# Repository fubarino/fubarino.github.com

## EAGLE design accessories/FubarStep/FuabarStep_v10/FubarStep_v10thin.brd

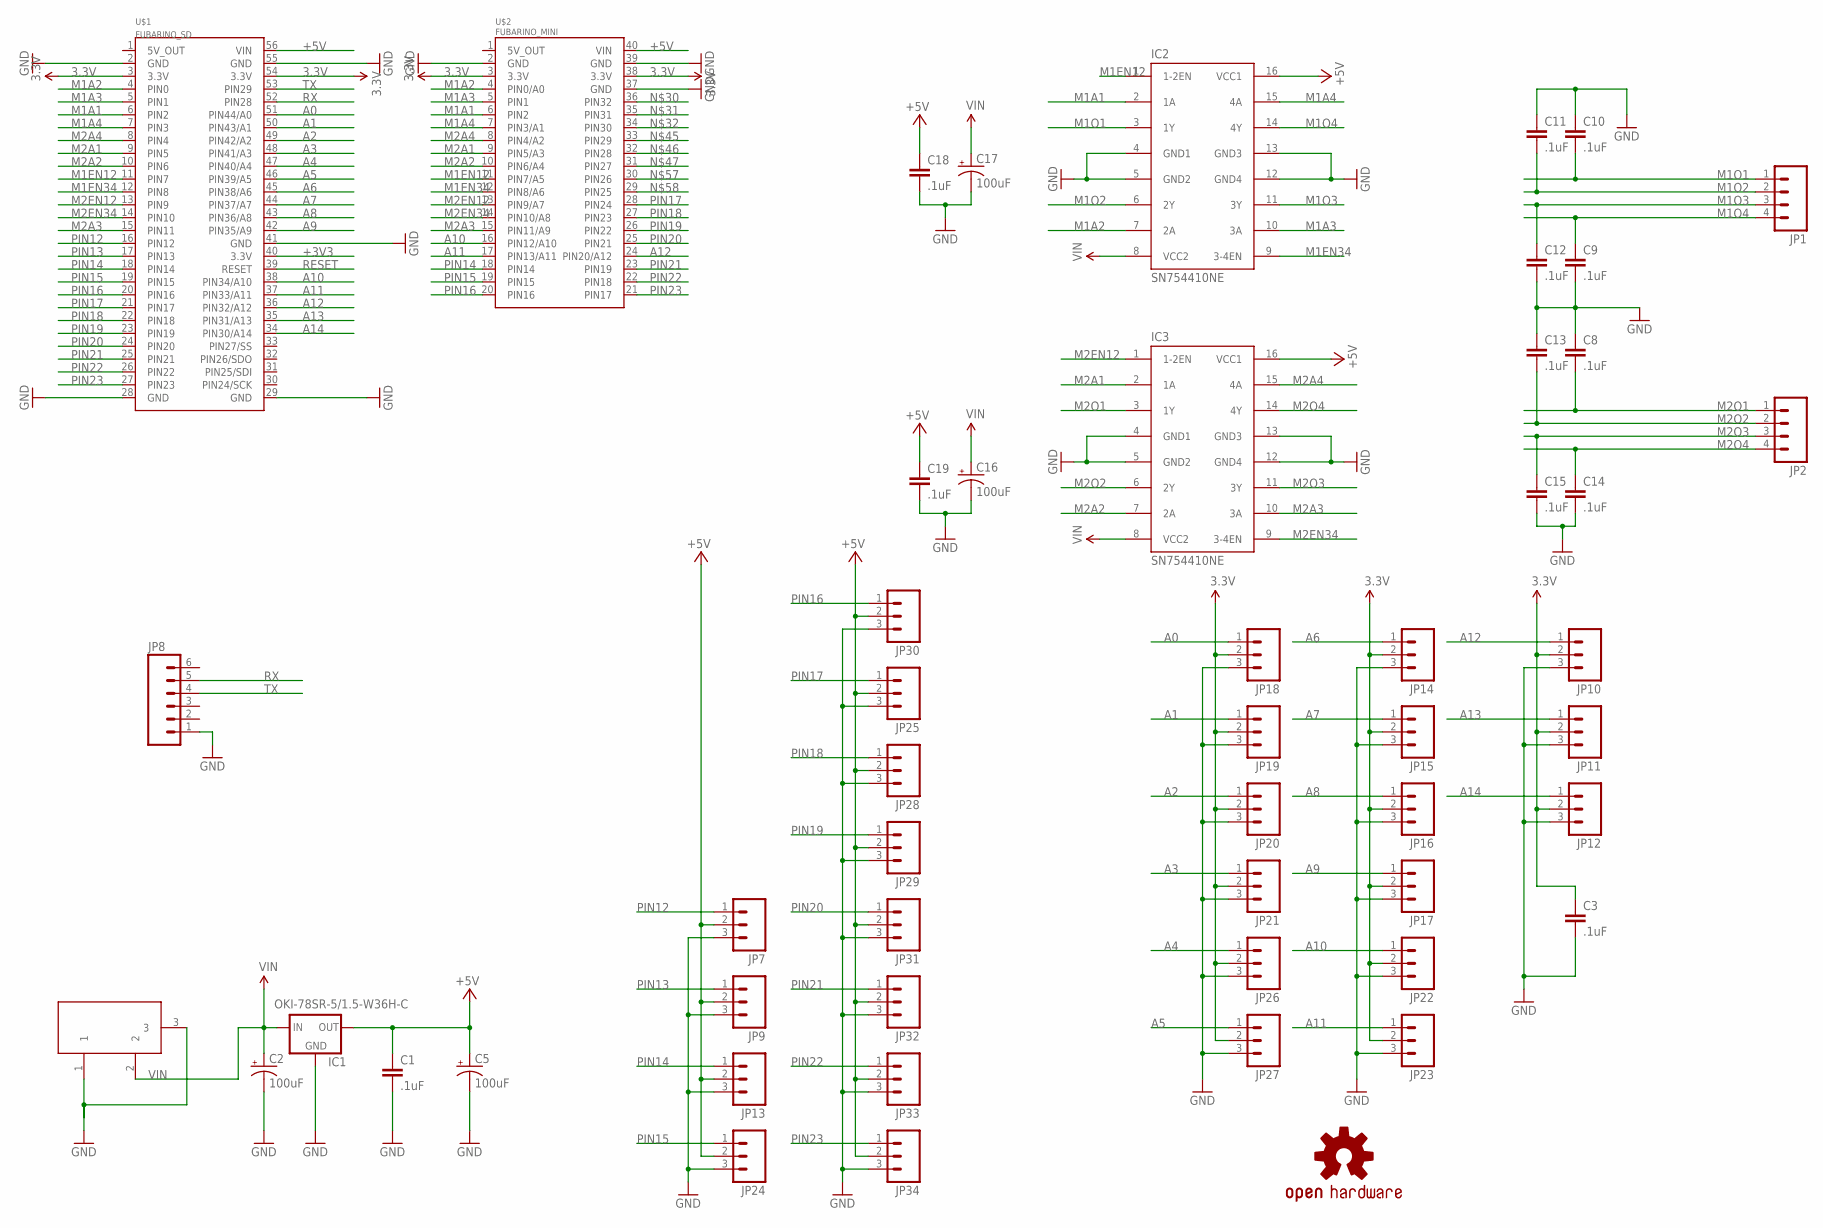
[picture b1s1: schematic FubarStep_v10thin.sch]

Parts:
C1, C3, C8, C9, C10, C11, C12, C13, C14, C15, C18, C19: .1uF; CAP-PTH-SMALL
C2, C5, C16, C17: 100uF; CPOL-RADIAL-100UF-25V
IC1: OKI-78SR-5/1.5-W36H-C; TO220-IGO
IC2, IC3: SN754410NE; DIL16
JP1, JP2: M04SCREW_LOCK; SCREWTERMINAL-3.5MM-4_LOCK
JP7, JP9, JP10, JP11, JP12, JP13, JP14, JP15, JP16, JP17, JP18, JP19, JP20, JP21, JP22, JP23, JP24, JP25, JP26, JP27, JP28, JP29, JP30, JP31, JP32, JP33, JP34: M03PTH; 1X03
JP8: M06LOCK; 1X06_LOCK
LOGO1: OSHW-LOGOM; OSHW-LOGO-M
U$1: FUBARINO_SD
U$2: FUBARINO_MINI
X1: DC21MMX; DC-21MM

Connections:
3.3V: C3.1, JP10.2, JP11.2, JP12.2, JP14.2, JP15.2, JP16.2, JP17.2, JP18.2, JP19.2, JP20.2, JP21.2, JP22.2, JP23.2, JP26.2, JP27.2, U$1.3 (3.3V), U$1.54 (3.3V), U$2.3 (3.3V), U$2.38 (3.3V)
+3V3: U$1.40 (3.3V)
+5V: C1.1, C5.1 (+), C18.1, C19.1, IC1.OUT, IC2.16 (VCC1), IC3.16 (VCC1), JP7.2, JP9.2, JP13.2, JP24.2, JP25.2, JP28.2, JP29.2, JP30.2, JP31.2, JP32.2, JP33.2, JP34.2, U$1.56 (VIN), U$2.40 (VIN)
A0: JP18.1, U$1.51 (PIN44/A0)
A1: JP19.1, U$1.50 (PIN43/A1)
A2: JP20.1, U$1.49 (PIN42/A2)
A3: JP21.1, U$1.48 (PIN41/A3)
A4: JP26.1, U$1.47 (PIN40/A4)
A5: JP27.1, U$1.46 (PIN39/A5)
A6: JP14.1, U$1.45 (PIN38/A6)
A7: JP15.1, U$1.44 (PIN37/A7)
A8: JP16.1, U$1.43 (PIN36/A8)
A9: JP17.1, U$1.42 (PIN35/A9)
A10: JP22.1, U$1.38 (PIN34/A10), U$2.16 (PIN12/A10)
A11: JP23.1, U$1.37 (PIN33/A11), U$2.17 (PIN13/A11)
A12: JP10.1, U$1.36 (PIN32/A12), U$2.24 (PIN20/A12)
A13: JP11.1, U$1.35 (PIN31/A13)
A14: JP12.1, U$1.34 (PIN30/A14)
GND: C1.2, C2.2 (-), C3.2, C5.2 (-), C8.1, C9.2, C10.1, C11.1, C12.2, C13.1, C14.2, C15.2, C16.2 (-), C17.2 (-), C18.2, C19.2, IC1.GND, IC2.4 (GND1), IC2.5 (GND2), IC2.12 (GND4), IC2.13 (GND3), IC3.4 (GND1), IC3.5 (GND2), IC3.12 (GND4), IC3.13 (GND3), JP7.3, JP8.1, JP9.3, JP10.3, JP11.3, JP12.3, JP13.3, JP14.3, JP15.3, JP16.3, JP17.3, JP18.3, JP19.3, JP20.3, JP21.3, JP22.3, JP23.3, JP24.3, JP25.3, JP26.3, JP27.3, JP28.3, JP29.3, JP30.3, JP31.3, JP32.3, JP33.3, JP34.3, U$1.2 (GND), U$1.28 (GND), U$1.29 (GND), U$1.41 (GND), U$1.55 (GND), U$2.2 (GND), U$2.37 (GND), U$2.39 (GND), X1.1, X1.3
M1A1: IC2.2 (1A), U$1.6 (PIN2), U$2.6 (PIN2)
M1A2: IC2.7 (2A), U$1.4 (PIN0), U$2.4 (PIN0/A0)
M1A3: IC2.10 (3A), U$1.5 (PIN1), U$2.5 (PIN1)
M1A4: IC2.15 (4A), U$1.7 (PIN3), U$2.7 (PIN3/A1)
M1EN12: IC2.1 (1-2EN), U$1.11 (PIN7), U$2.11 (PIN7/A5)
M1EN34: IC2.9 (3-4EN), U$1.12 (PIN8), U$2.12 (PIN8/A6)
M1O1: C10.2, IC2.3 (1Y), JP1.1
M1O2: C11.2, IC2.6 (2Y), JP1.2
M1O3: C12.1, IC2.11 (3Y), JP1.3
M1O4: C9.1, IC2.14 (4Y), JP1.4
M2A1: IC3.2 (1A), U$1.9 (PIN5), U$2.9 (PIN5/A3)
M2A2: IC3.7 (2A), U$1.10 (PIN6), U$2.10 (PIN6/A4)
M2A3: IC3.10 (3A), U$1.15 (PIN11), U$2.15 (PIN11/A9)
M2A4: IC3.15 (4A), U$1.8 (PIN4), U$2.8 (PIN4/A2)
M2EN12: IC3.1 (1-2EN), U$1.13 (PIN9), U$2.13 (PIN9/A7)
M2EN34: IC3.9 (3-4EN), U$1.14 (PIN10), U$2.14 (PIN10/A8)
M2O1: C8.2, IC3.3 (1Y), JP2.1
M2O2: C13.2, IC3.6 (2Y), JP2.2
M2O3: C15.1, IC3.11 (3Y), JP2.3
M2O4: C14.1, IC3.14 (4Y), JP2.4
PIN12: JP7.1, U$1.16 (PIN12)
PIN13: JP9.1, U$1.17 (PIN13)
PIN14: JP13.1, U$1.18 (PIN14), U$2.18 (PIN14)
PIN15: JP24.1, U$1.19 (PIN15), U$2.19 (PIN15)
PIN16: JP30.1, U$1.20 (PIN16), U$2.20 (PIN16)
PIN17: JP25.1, U$1.21 (PIN17), U$2.28 (PIN24)
PIN18: JP28.1, U$1.22 (PIN18), U$2.27 (PIN23)
PIN19: JP29.1, U$1.23 (PIN19), U$2.26 (PIN22)
PIN20: JP31.1, U$1.24 (PIN20), U$2.25 (PIN21)
PIN21: JP32.1, U$1.25 (PIN21), U$2.23 (PIN19)
PIN22: JP33.1, U$1.26 (PIN22), U$2.22 (PIN18)
PIN23: JP34.1, U$1.27 (PIN23), U$2.21 (PIN17)
RESET: U$1.39 (RESET)
RX: JP8.5, U$1.52 (PIN28)
TX: JP8.4, U$1.53 (PIN29)
VIN: C2.1 (+), C16.1 (+), C17.1 (+), IC1.IN, IC2.8 (VCC2), IC3.8 (VCC2), X1.2

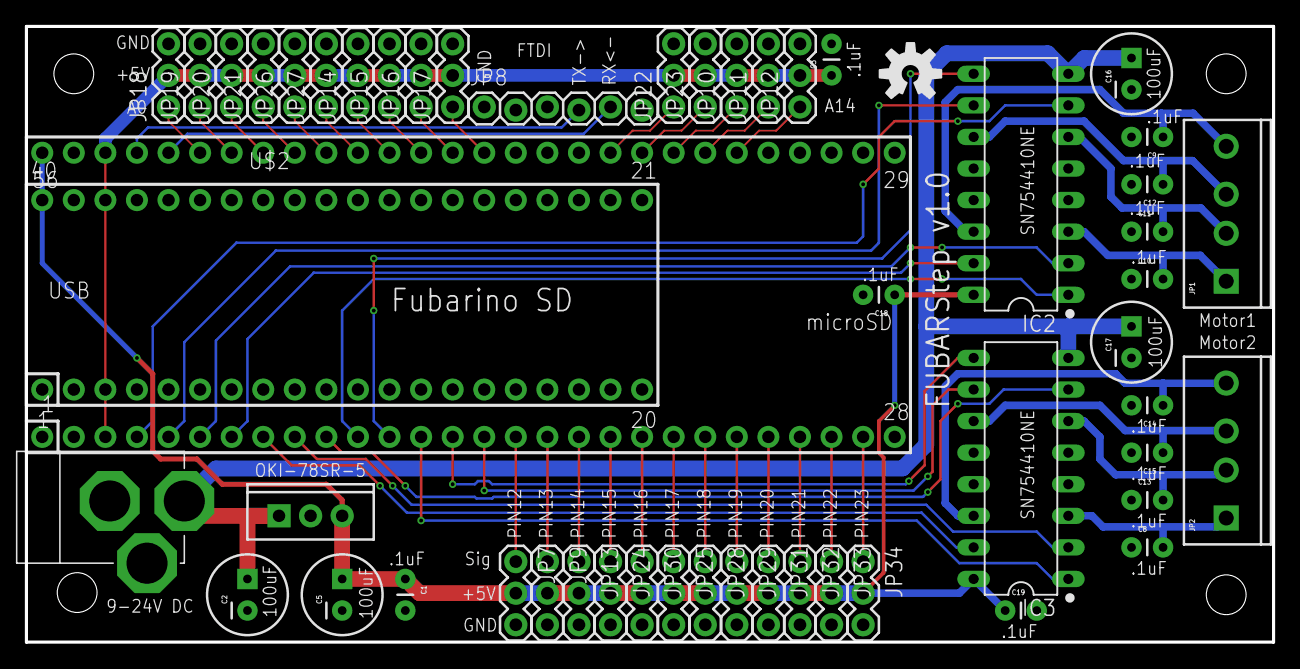
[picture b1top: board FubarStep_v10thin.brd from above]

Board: 2 copper layers, 100.3 x 49.5 mm, 53 parts (0 on the bottom side), 53 nets.

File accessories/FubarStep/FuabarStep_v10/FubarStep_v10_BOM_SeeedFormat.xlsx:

Electronic Engineering BOM List
Product Name： FubarStep
Version：V1.0
Issue Date：03/13/2013
Item No. (序号) | Reference Des (上件位置) | Qty (用量) | Catalog (分类） | Part_Description (规格描述) | Part_Value （元件值） | Part_Package （元件封装） | Manufacturers Name (使用厂牌名称) | Manufacturers Part No. (使用厂牌型号) | Distributors Name （供应商名称） | Distributors Part No. (供貨商型号) | Unit Price （单价） | Price Break To Use （价格分段的购买量） | Notes/Remark （备注）
Example（填写范例）
1 | U1 | 2 | Connector | 28 pin female .100" header for Fubarino SD footprint |  |  |  |  |  |  |  |  | 0
2 | U2 | 2 | Connector | 20 pin female .100" header for Fubarino Mini footprint |  |  |  |  |  |  |  |  | 0
3 | JP7,JP9,JP13,JP24,JP30,JP25,JP28,JP29,JP31,JP32,JP33, | 3 | Connector | 12 pin male .100" header for servo connections |  |  |  |  |  |  |  |  | 0
4 | JP18,JP19,JP20,Jp21,JP26,JP27,JP14,JP15,JP16,JP17,Jp22,JP23,JP10,JP11,JP12 | 3 | Connector | 15 pin male .100" header for analog connections |  |  |  |  |  |  |  |  | 0
5 | C3,C11,C10,C12,C9,C13,C8,C15,C14,C18,C19,C1 | 12 | Capacitor | .1uF through hole ceramic capactor |  |  | Murata | RPER71H104K2P1A03B | Arrow | RPER71H104K2P1A03B | 4.8500000000000001E-2 |  | 0.58200000000000007
6 | C5,C2,C17,C16 | 4 | Capacitor | 100uF >35V electrolytic through hole capacitor |  |  | Nichicon | UVR1H101MPD | Arrow | UVR1H101MPD | 4.2599999999999999E-2 |  | 0.1704
7 | IC2,IC3 | 2 | IC | SN754410NE H-Bridge in 16 PDIP |  |  | Texas Instruments | SN754410NE | Arrow | SN754410NE | 0.88990000000000002 |  | 1.7798
8 | SOC1,SOC2 | 2 | Connector | 16 PDIP socket for IC2, IC3 |  |  |  |  |  |  |  |  | 0
9 | JP1, JP2 | 2 | Connector | 4-pin 3.5mm screw terminal |  |  |  |  |  |  |  |  | 0
10 | JP8 | 1 | Connector | 6-pin right angle .100 male header |  |  |  |  |  |  |  |  | 0
11 | JP3 | 1 | Connector | 3-pin male .100 header for power select |  |  |  |  |  |  |  |  | 0
12 | JP4 | 1 | Connector | 2-pin 3.5mm screw terminal |  |  |  |  |  |  |  |  | 0
13 | X1 | 1 | Connector | barrel jack power input |  |  |  |  |  |  |  |  | 0
14 | U3 | 1 | IC | 5V switching regulator |  |  | Murata Power Solutions | OKI-78SR-5/1.5-W36H-C | DigiKey | 811-2196-5-ND | 4.3 |  | 4.3
15 | JP3_JUMP | 1 | Connector | .100 2-pin shorting jumper |  |  |  |  |  |  |  |  | 0
16 | PCB | 1 | OTHER | FubarStep v1.0 PCB |  |  | SeeedStudio |  |  |  | 3.4 |  | 3.4
 |  |  |  |  |  |  |  |  |  |  |  |  | 0
 |  |  |  |  |  |  |  |  |  |  |  | Total | 10.232200000000001
1. Recommended Distributor: Digi-Key, Mouser, Avnet Express, Farnell.
2. Catalog: Capacitor,Resister,Diode,Connector,Transistor,IC,PROTECTOR CATEGORY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
3. Required Fields: Item No, Reference Des, Qty, Catalog, Part_Value, Part Pack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
Optional Fields: Part_Description, Manufacturers Name, Manufacturers Part No, D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

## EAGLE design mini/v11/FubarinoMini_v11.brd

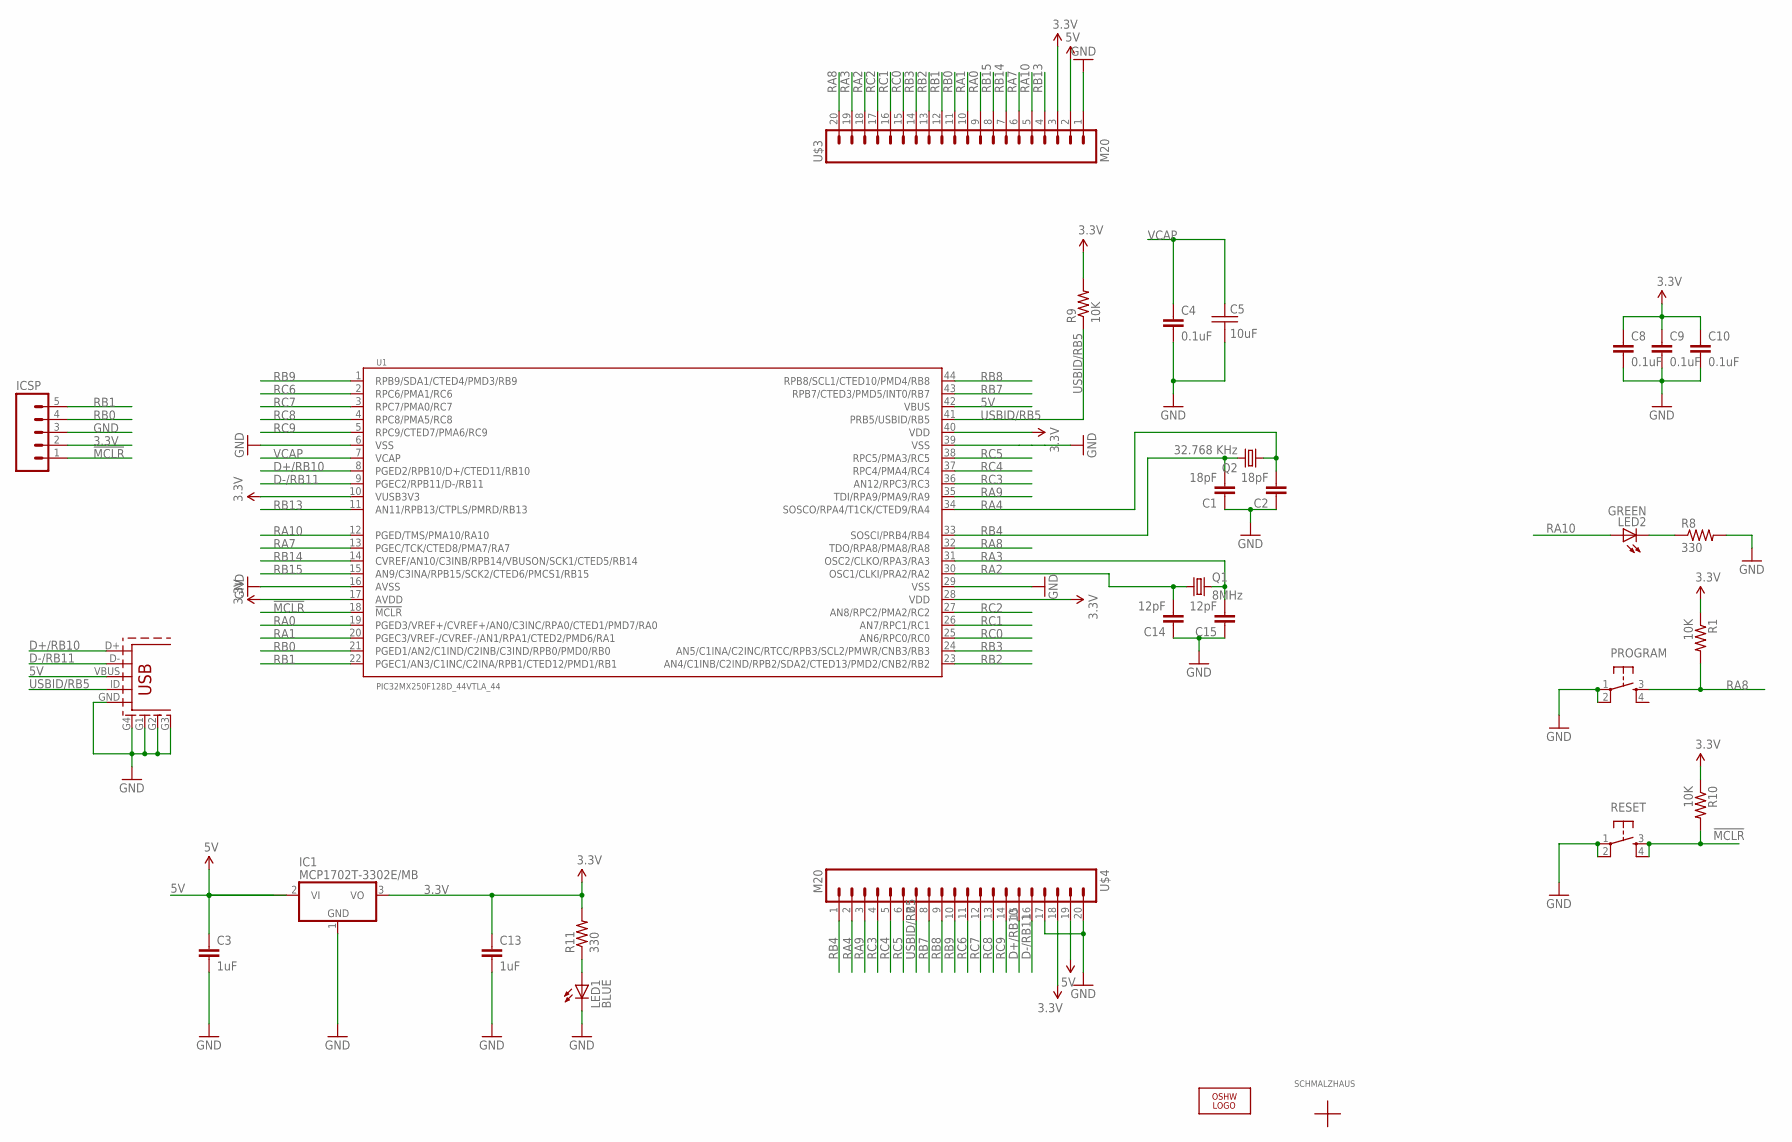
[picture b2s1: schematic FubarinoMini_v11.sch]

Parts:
C1, C2: 18pF; 0603-CAP
C3: 1uF; 0603-CAP
C4, C8, C9: 0.1uF; 0603-CAP
C5: 10uF; CAP_0805
C10: 0.1uF; 0603
C13: 1uF; 0603
C14, C15: 12pF; 0603-CAP
IC1: MCP1702T-3302E/MB; SOT89
ICSP: M05NOSLILK; 1X05_NOSILK
J8: USB_5PIN; USB-MINIB
LED1: BLUE; LED-0603
LED2: GREEN; LED-0603
LOGO1: OSHW_LOGO_8MILX0070-NT; OSHW_8X70_NOTEXT
PROGRAM: TAC_SWITCHSND; TACTILE_SWITCH_SMD
Q1: 8MHz; NX5032_5MM_3.2MM_CRYSTAL
Q2: 32.768 KHz; TC26H
R1, R9, R10: 10K; 0603-RES
R8, R11: 330; 0603-RES
RESET: TAC_SWITCHSND; TACTILE_SWITCH_SMD
U1: PIC32MX250F128D_44VTLA_44; VTLA_44
U$1: SCHMALZHAUSSCHMALZHAUS_SMALL; SCHMALZHAUS_SMALL
U$3, U$4: M20; 1X20_NO_PIN1

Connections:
3.3V: C8.1, C9.1, C10.1, C13.1, IC1.3 (VO), ICSP.2, R1.1, R9.2, R10.1, R11.2, U1.10 (VUSB3V3), U1.17 (AVDD), U1.28 (VDD), U1.40 (VDD), U$3.3, U$4.18
5V: C3.1, IC1.2 (VI), IC1.2@1 (VI1), J8.VBUS, U1.42 (VBUS), U$3.2, U$4.19
!MCLR!: ICSP.1, R10.2, RESET.3, RESET.4, U1.18 (!MCLR!)
D+/RB10: J8.D+, U1.8 (PGED2/RPB10/D+/CTED11/RB10), U$4.15
D-/RB11: J8.D-, U1.9 (PGEC2/RPB11/D-/RB11), U$4.16
GND: C1.1, C2.1, C3.2, C4.2, C5.2, C8.2, C9.2, C10.2, C13.2, C14.1, C15.1, IC1.1 (GND), ICSP.3, J8.G1, J8.G2, J8.G3, J8.G4 (SHIELD), J8.GND, LED1.C, PROGRAM.1, PROGRAM.2, R8.2, RESET.1, RESET.2, U1.6 (VSS), U1.16 (AVSS), U1.29 (VSS), U1.39 (VSS), U$3.1, U$4.17, U$4.20
unnamed: LED1.A, R11.1
unnamed: LED2.C, R8.1
RA0: U1.19 (PGED3/VREF+/CVREF+/AN0/C3INC/RPA0/CTED1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), U$3.9
RA1: U1.20 (PGEC3/VREF-/CVREF-/AN1/RPA1/CTED2/PMD6/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), U$3.10
RA2: C14.2, Q1.1, U1.30 (OSC1/CLKI/PRA2/RA2), U$3.18
RA3: C15.2, Q1.2, U1.31 (OSC2/CLKO/RPA3/RA3), U$3.19
RA4: C2.2, Q2.1, U1.34 (SOSCO/RPA4/T1CK/CTED9/RA4), U$4.2
RA7: U1.13 (PGEC/TCK/CTED8/PMA7/RA7), U$3.6
RA8: PROGRAM.3, R1.2, U1.32 (TDO/RPA8/PMA8/RA8), U$3.20
RA9: U1.35 (TDI/RPA9/PMA9/RA9), U$4.3
RA10: LED2.A, U1.12 (PGED/TMS/PMA10/RA10), U$3.5
RB0: ICSP.4, U1.21 (PGED1/AN2/C1IND/C2INB/C3IND/RPB0/PMD0/R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), U$3.11
RB1: ICSP.5, U1.22 (PGEC1/AN3/C1INC/C2INA/RPB1/CTED12/PMD1/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), U$3.12
RB2: U1.23 (AN4/C1INB/C2IND/RPB2/SDA2/CTED13/PMD2/C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), U$3.13
RB3: U1.24 (AN5/C1INA/C2INC/RTCC/RPB3/SCL2/PMWR/CNB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), U$3.14
RB4: C1.2, Q2.2, U1.33 (SOSCI/PRB4/RB4), U$4.1
RB7: U1.43 (RPB7/CTED3/PMD5/INT0/RB7), U$4.8
RB8: U1.44 (RPB8/SCL1/CTED10/PMD4/RB8), U$4.9
RB9: U1.1 (RPB9/SDA1/CTED4/PMD3/RB9), U$4.10
RB13: U1.11 (AN11/RPB13/CTPLS/PMRD/RB13), U$3.4
RB14: U1.14 (CVREF/AN10/C3INB/RPB14/VBUSON/SCK1/CTED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), U$3.7
RB15: U1.15 (AN9/C3INA/RPB15/SCK2/CTED6/PMCS1/RB15), U$3.8
RC0: U1.25 (AN6/RPC0/RC0), U$3.15
RC1: U1.26 (AN7/RPC1/RC1), U$3.16
RC2: U1.27 (AN8/RPC2/PMA2/RC2), U$3.17
RC3: U1.36 (AN12/RPC3/RC3), U$4.4
RC4: U1.37 (RPC4/PMA4/RC4), U$4.5
RC5: U1.38 (RPC5/PMA3/RC5), U$4.6
RC6: U1.2 (RPC6/PMA1/RC6), U$4.11
RC7: U1.3 (RPC7/PMA0/RC7), U$4.12
RC8: U1.4 (RPC8/PMA5/RC8), U$4.13
RC9: U1.5 (RPC9/CTED7/PMA6/RC9), U$4.14
USBID/RB5: J8.ID (USB_ID), R9.1, U1.41 (PRB5/USBID/RB5), U$4.7
VCAP: C4.1, C5.1, U1.7 (VCAP)

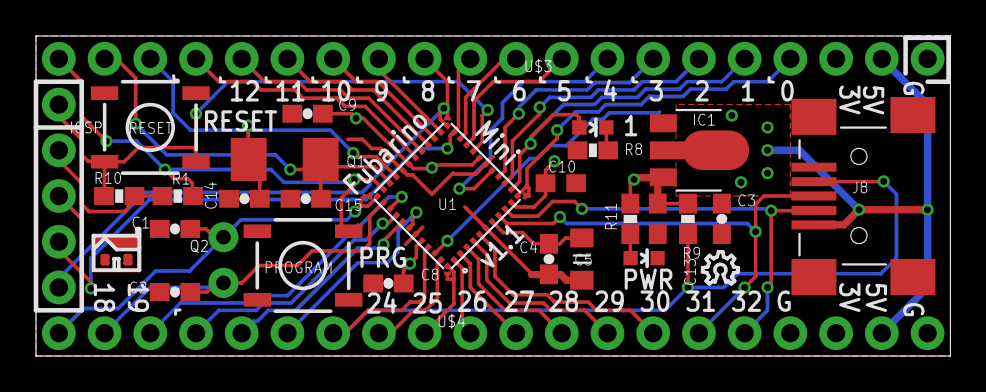
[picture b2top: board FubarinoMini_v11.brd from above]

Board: 2 copper layers, 50.8 x 17.8 mm, 30 parts (0 on the bottom side), 40 nets.

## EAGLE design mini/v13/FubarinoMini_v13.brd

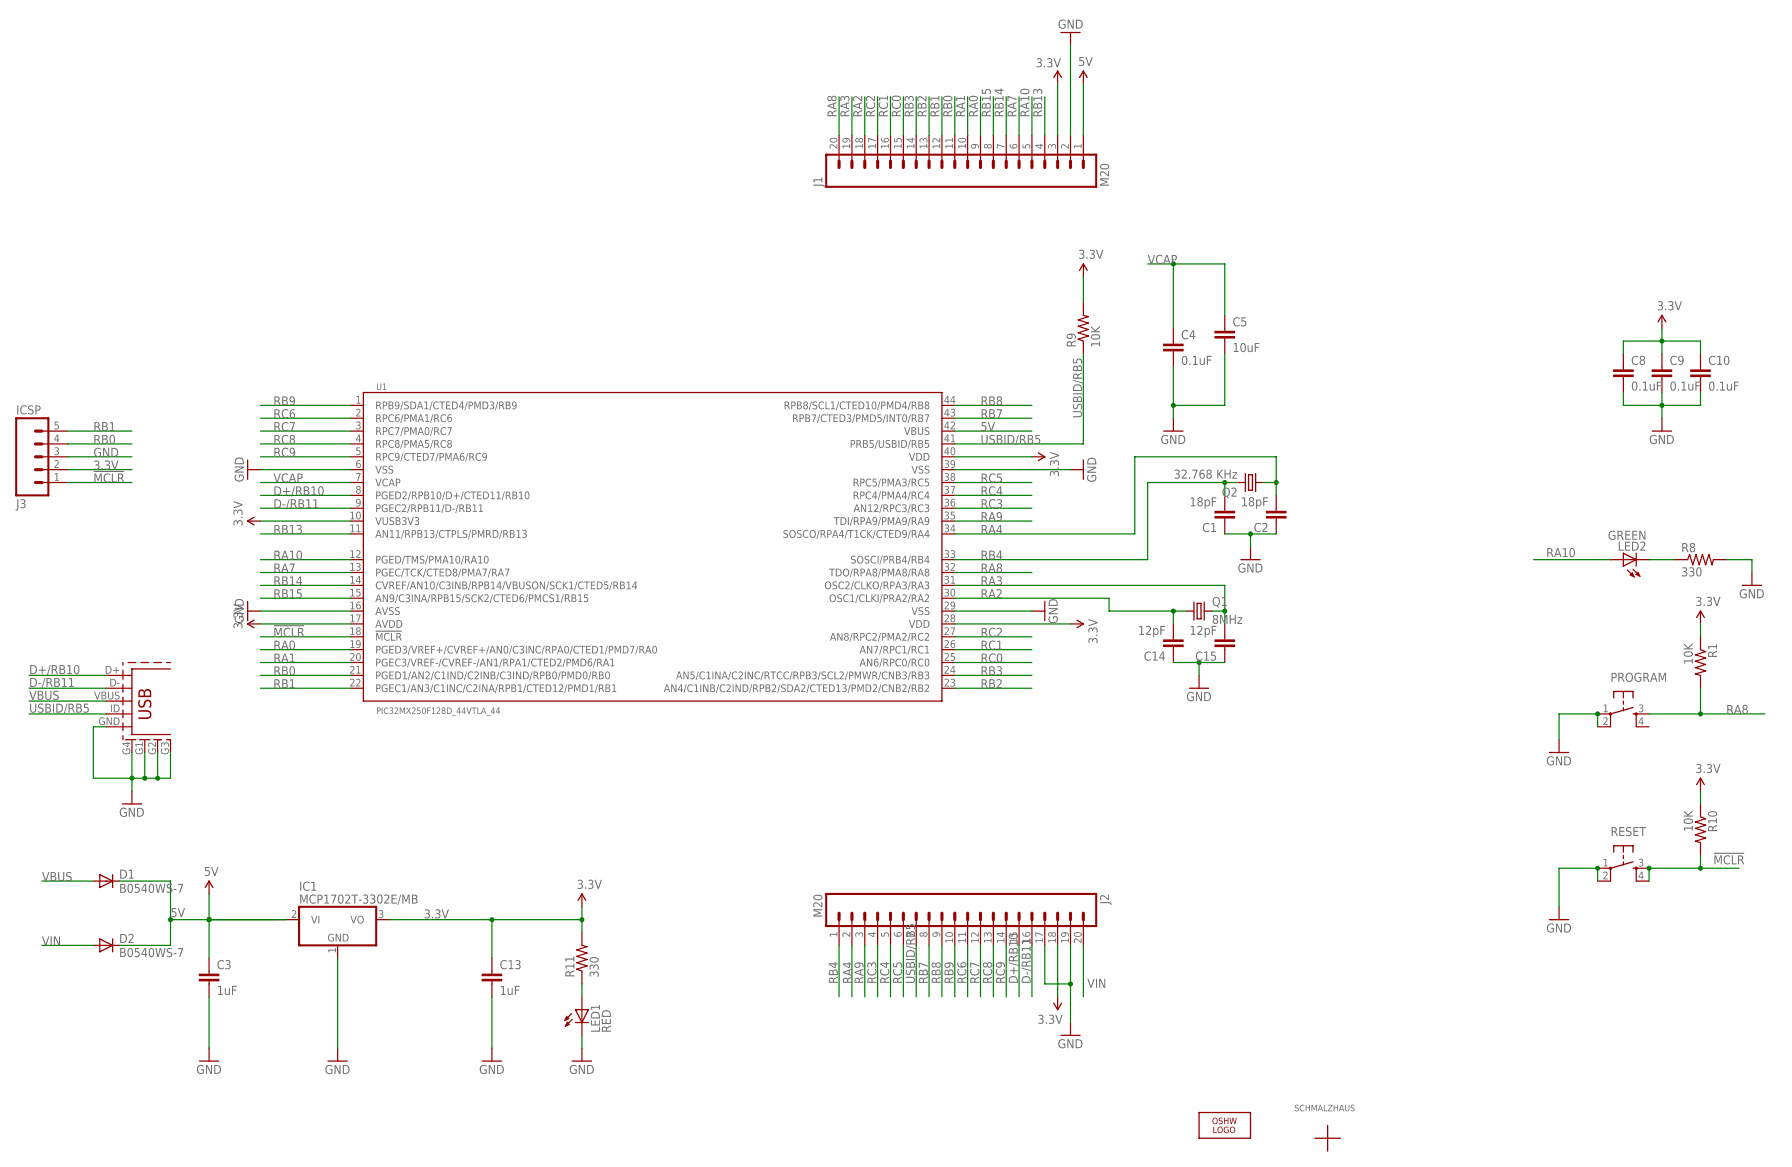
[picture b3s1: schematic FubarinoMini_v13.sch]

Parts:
C1, C2: 18pF; 0603-CAP
C3: 1uF; 0603-CAP
C4, C8, C9: 0.1uF; 0603-CAP
C5: 10uF; 0805
C10: 0.1uF; 0603
C13: 1uF; 0603
C14, C15: 12pF; 0603-CAP
D1, D2: B0540WS-7; SOD-323
IC1: MCP1702T-3302E/MB; SOT89
ICSP: J3; 1X05_NOSILK
J1, J2: M20; 1X20_NO_PIN1
J8: USB_5PIN; USB-MINIB
LED1: RED; LED-0603
LED2: GREEN; LED-0603
LOGO1: OSHW_LOGO_8MILX0070-NT; OSHW_8X70_NOTEXT
PROGRAM: TAC_SWITCHSND; TACTILE_SWITCH_SMD
Q1: 8MHz; NX5032_5MM_3.2MM_CRYSTAL
Q2: 32.768 KHz; TC26H
R1, R9, R10: 10K; 0603-RES
R8, R11: 330; 0603-RES
RESET: TAC_SWITCHSND; TACTILE_SWITCH_SMD
U1: PIC32MX250F128D_44VTLA_44; VTLA_44
U$1: SCHMALZHAUSSCHMALZHAUS_SMALL; SCHMALZHAUS_SMALL

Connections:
3.3V: C8.1, C9.1, C10.1, C13.1, IC1.3 (VO), ICSP.2, J1.3, J2.18, R1.1, R9.2, R10.1, R11.2, U1.10 (VUSB3V3), U1.17 (AVDD), U1.28 (VDD), U1.40 (VDD)
5V: C3.1, D1.1 (C), D2.1 (C), IC1.2 (VI), IC1.2@1 (VI1), J1.1, U1.42 (VBUS)
!MCLR!: ICSP.1, R10.2, RESET.3, RESET.4, U1.18 (!MCLR!)
D+/RB10: J2.15, J8.D+, U1.8 (PGED2/RPB10/D+/CTED11/RB10)
D-/RB11: J2.16, J8.D-, U1.9 (PGEC2/RPB11/D-/RB11)
GND: C1.1, C2.1, C3.2, C4.2, C5.2, C8.2, C9.2, C10.2, C13.2, C14.1, C15.1, IC1.1 (GND), ICSP.3, J1.2, J2.17, J2.19, J8.G1, J8.G2, J8.G3, J8.G4 (SHIELD), J8.GND, LED1.C, PROGRAM.1, PROGRAM.2, R8.2, RESET.1, RESET.2, U1.6 (VSS), U1.16 (AVSS), U1.29 (VSS), U1.39 (VSS)
unnamed: LED1.A, R11.1
unnamed: LED2.C, R8.1
RA0: J1.9, U1.19 (PGED3/VREF+/CVREF+/AN0/C3INC/RPA0/CTED1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)
RA1: J1.10, U1.20 (PGEC3/VREF-/CVREF-/AN1/RPA1/CTED2/PMD6/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)
RA2: C14.2, J1.18, Q1.1, U1.30 (OSC1/CLKI/PRA2/RA2)
RA3: C15.2, J1.19, Q1.2, U1.31 (OSC2/CLKO/RPA3/RA3)
RA4: C2.2, J2.2, Q2.1, U1.34 (SOSCO/RPA4/T1CK/CTED9/RA4)
RA7: J1.6, U1.13 (PGEC/TCK/CTED8/PMA7/RA7)
RA8: J1.20, PROGRAM.3, R1.2, U1.32 (TDO/RPA8/PMA8/RA8)
RA9: J2.3, U1.35 (TDI/RPA9/PMA9/RA9)
RA10: J1.5, LED2.A, U1.12 (PGED/TMS/PMA10/RA10)
RB0: ICSP.4, J1.11, U1.21 (PGED1/AN2/C1IND/C2INB/C3IND/RPB0/PMD0/R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)
RB1: ICSP.5, J1.12, U1.22 (PGEC1/AN3/C1INC/C2INA/RPB1/CTED12/PMD1/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)
RB2: J1.13, U1.23 (AN4/C1INB/C2IND/RPB2/SDA2/CTED13/PMD2/C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)
RB3: J1.14, U1.24 (AN5/C1INA/C2INC/RTCC/RPB3/SCL2/PMWR/CNB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)
RB4: C1.2, J2.1, Q2.2, U1.33 (SOSCI/PRB4/RB4)
RB7: J2.8, U1.43 (RPB7/CTED3/PMD5/INT0/RB7)
RB8: J2.9, U1.44 (RPB8/SCL1/CTED10/PMD4/RB8)
RB9: J2.10, U1.1 (RPB9/SDA1/CTED4/PMD3/RB9)
RB13: J1.4, U1.11 (AN11/RPB13/CTPLS/PMRD/RB13)
RB14: J1.7, U1.14 (CVREF/AN10/C3INB/RPB14/VBUSON/SCK1/CTED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)
RB15: J1.8, U1.15 (AN9/C3INA/RPB15/SCK2/CTED6/PMCS1/RB15)
RC0: J1.15, U1.25 (AN6/RPC0/RC0)
RC1: J1.16, U1.26 (AN7/RPC1/RC1)
RC2: J1.17, U1.27 (AN8/RPC2/PMA2/RC2)
RC3: J2.4, U1.36 (AN12/RPC3/RC3)
RC4: J2.5, U1.37 (RPC4/PMA4/RC4)
RC5: J2.6, U1.38 (RPC5/PMA3/RC5)
RC6: J2.11, U1.2 (RPC6/PMA1/RC6)
RC7: J2.12, U1.3 (RPC7/PMA0/RC7)
RC8: J2.13, U1.4 (RPC8/PMA5/RC8)
RC9: J2.14, U1.5 (RPC9/CTED7/PMA6/RC9)
USBID/RB5: J2.7, J8.ID (USB_ID), R9.1, U1.41 (PRB5/USBID/RB5)
VBUS: D1.2 (A), J8.VBUS
VCAP: C4.1, C5.1, U1.7 (VCAP)
VIN: D2.2 (A), J2.20

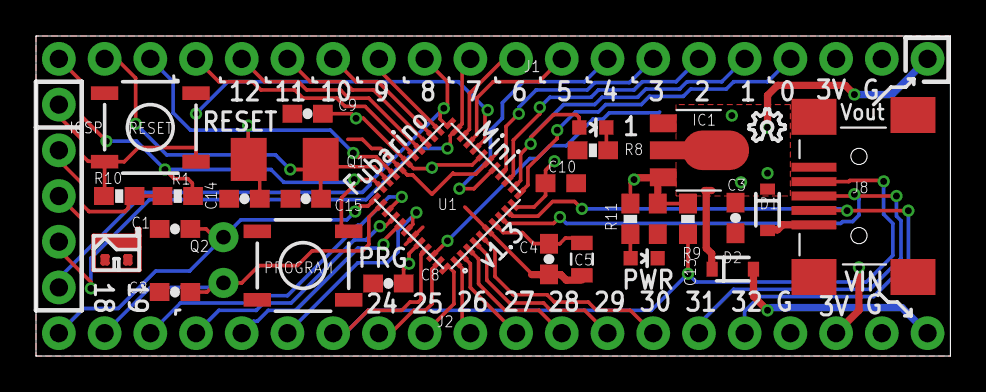
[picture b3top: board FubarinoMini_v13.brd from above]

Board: 2 copper layers, 50.8 x 17.8 mm, 32 parts (0 on the bottom side), 42 nets.

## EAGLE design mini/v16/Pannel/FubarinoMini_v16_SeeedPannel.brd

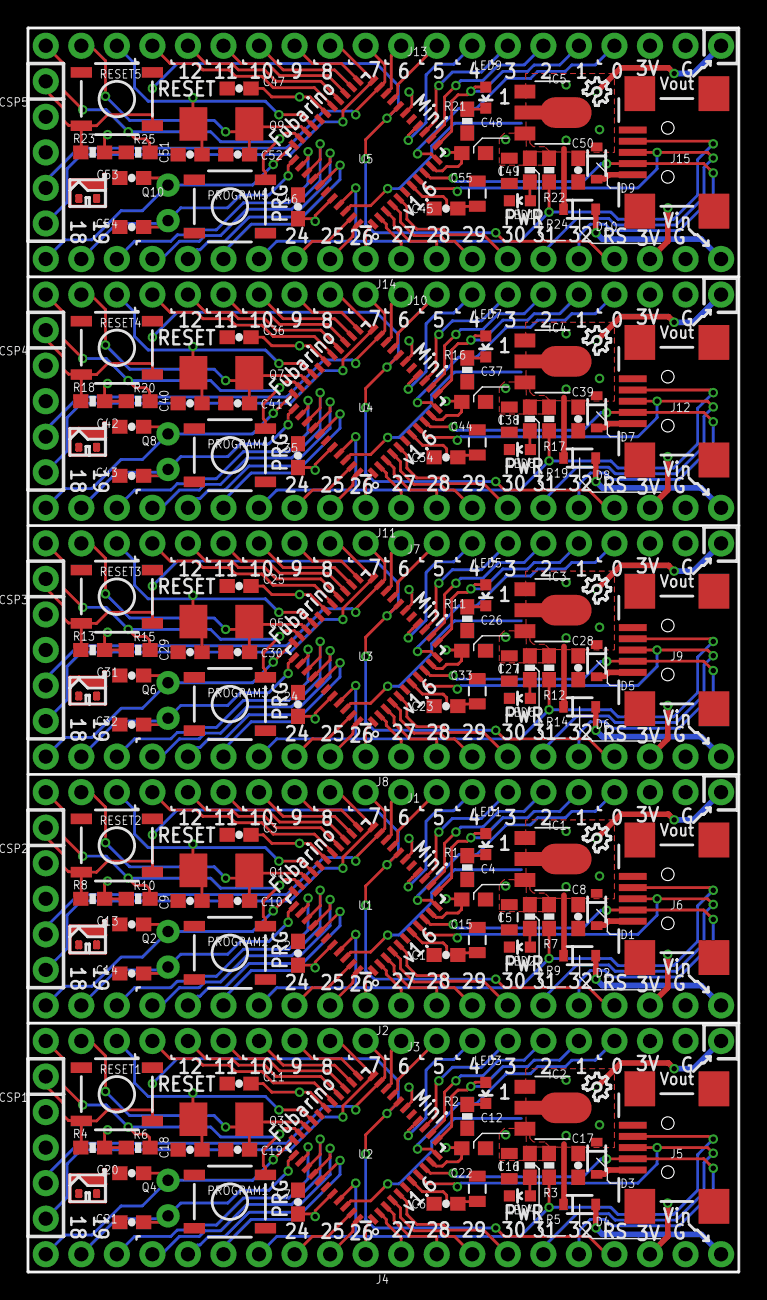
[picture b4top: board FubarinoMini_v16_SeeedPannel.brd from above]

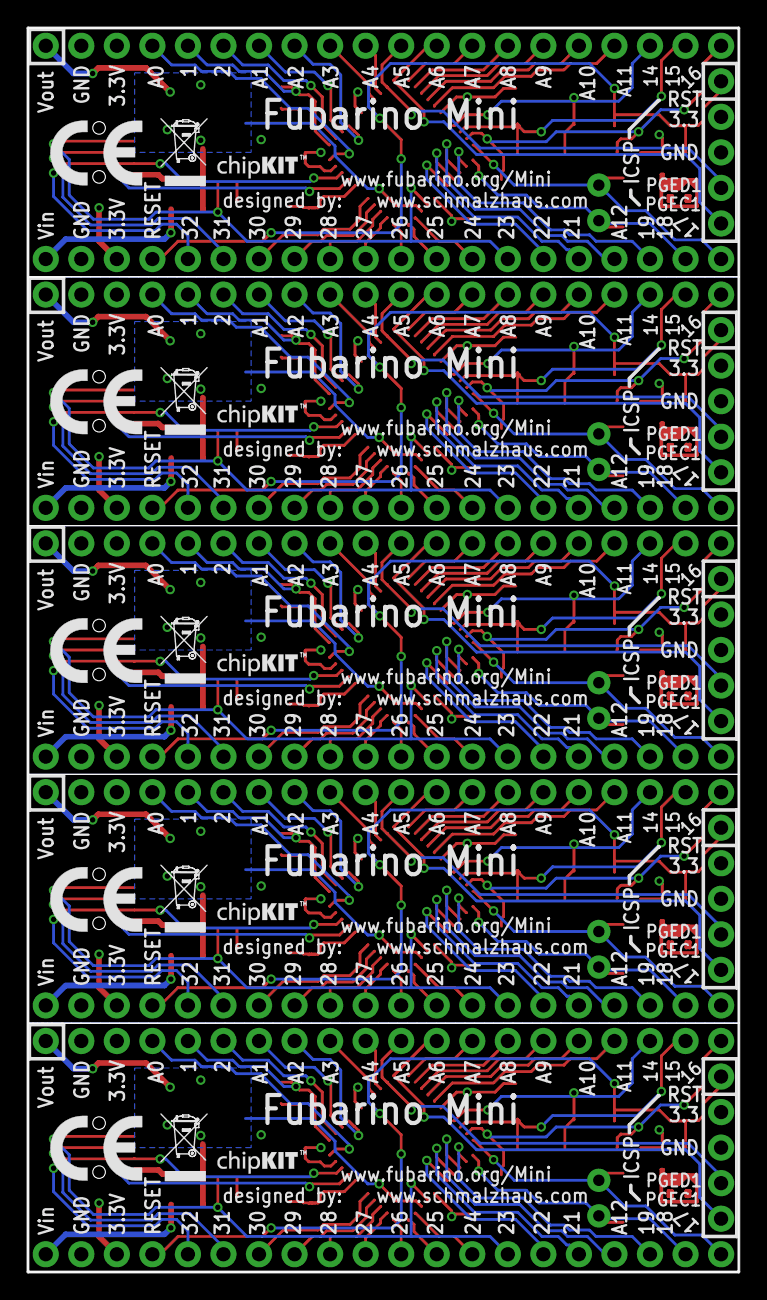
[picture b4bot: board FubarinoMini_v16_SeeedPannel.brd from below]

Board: 2 copper layers, 50.8 x 88.9 mm, 175 parts (15 on the bottom side), 210 nets.

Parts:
C1, C2, C3, C6, C7, C11, C23, C24, C25, C34, C35, C36, C45, C46, C47: 0.1uF; 0603-CAP
C4, C12, C26, C37, C48: 0.1uF; 0603
C5, C15, C16, C22, C27, C33, C38, C44, C49, C55: 10uF; 0805
C8, C17, C28, C39, C50: 1uF; 0603-CAP
C9, C10, C18, C19, C29, C30, C40, C41, C51, C52: 12pF; 0603-CAP
C13, C14, C20, C21, C31, C32, C42, C43, C53, C54: 18pF; 0603-CAP
D1, D2, D3, D4, D5, D6, D7, D8, D9, D10: B0540WS-7; SOD-323
IC1, IC2, IC3, IC4, IC5: MCP1702T-3302E/MB; SOT89
ICSP1, ICSP2, ICSP3, ICSP4, ICSP5: J3; 1X05_NOSILK
J1, J2, J3, J4, J7, J8, J10, J11, J13, J14: M20; 1X20_NO_PIN1
J5, J6, J9, J12, J15: USB-5PIN; USB-MINIB-5PIN-HIROSE-UX60-MB-5ST
LED1, LED3, LED5, LED7, LED9: GREEN; LED-0603
LED2, LED4, LED6, LED8, LED10: RED; LED-0603
LOGO1, LOGO2, LOGO3, LOGO4, LOGO5: OSHW_LOGO_8MILX0070-NT; OSHW_8X70_NOTEXT
PROGRAM1, PROGRAM2, PROGRAM3, PROGRAM4, PROGRAM5: TACTILE_SWITCH_SMD
Q1, Q3, Q5, Q7, Q9: 8MHz; NX5032_5MM_3.2MM_CRYSTAL
Q2, Q4, Q6, Q8, Q10: 32.768 KHz; TC26H
R1, R2, R5, R9, R11, R14, R16, R19, R21, R24: 330; 0603-RES
R3, R4, R6, R7, R8, R10, R12, R13, R15, R17, R18, R20, R22, R23, R25: 10K; 0603-RES
RESET1, RESET2, RESET3, RESET4, RESET5: TACTILE_SWITCH_SMD
U1, U2, U3, U4, U5: PIC32MX250F128D_44VTLA_44; QFN-44-8X8-NOPAD
U$1, U$5, U$9, U$13, U$17: SCHMALZHAUSSCHMALZHAUS_SMALL; SCHMALZHAUS_SMALL
U$2, U$6, U$10, U$14, U$18: CE_MARK5MM; CE_5MM
U$3, U$7, U$11, U$15, U$19: ROSH_GARBAGE; ROHS_GARBAGE_5MM
U$4, U$8, U$12, U$16, U$20: CHIPKIT2MM; CHIPKIT_2MM

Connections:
3.3V1: C7.1, C11.1, C12.1, C16.1, IC2.3, ICSP1.2, J3.3, J4.18, R3.2, R4.1, R5.2, R6.1, U2.10, U2.17, U2.28, U2.40
3.3V2: C2.1, C3.1, C4.1, C5.1, IC1.3, ICSP2.2, J1.3, J2.18, R7.2, R8.1, R9.2, R10.1, U1.10, U1.17, U1.28, U1.40
3.3V3: C24.1, C25.1, C26.1, C27.1, IC3.3, ICSP3.2, J7.3, J8.18, R12.2, R13.1, R14.2, R15.1, U3.10, U3.17, U3.28, U3.40
3.3V4: C35.1, C36.1, C37.1, C38.1, IC4.3, ICSP4.2, J10.3, J11.18, R17.2, R18.1, R19.2, R20.1, U4.10, U4.17, U4.28, U4.40
3.3V5: C46.1, C47.1, C48.1, C49.1, IC5.3, ICSP5.2, J13.3, J14.18, R22.2, R23.1, R24.2, R25.1, U5.10, U5.17, U5.28, U5.40
5V1: C17.1, D3.1, D4.1, IC2.2, IC2.2@1, J3.1, U2.42
5V2: C8.1, D1.1, D2.1, IC1.2, IC1.2@1, J1.1, U1.42
5V3: C28.1, D5.1, D6.1, IC3.2, IC3.2@1, J7.1, U3.42
5V4: C39.1, D7.1, D8.1, IC4.2, IC4.2@1, J10.1, U4.42
5V5: C50.1, D9.1, D10.1, IC5.2, IC5.2@1, J13.1, U5.42
!MCLR!1: ICSP1.1, J4.17, R4.2, RESET1.3, RESET1.4, U2.18
!MCLR!2: ICSP2.1, J2.17, R8.2, RESET2.3, RESET2.4, U1.18
!MCLR!3: ICSP3.1, J8.17, R13.2, RESET3.3, RESET3.4, U3.18
!MCLR!4: ICSP4.1, J11.17, R18.2, RESET4.3, RESET4.4, U4.18
!MCLR!5: ICSP5.1, J14.17, R23.2, RESET5.3, RESET5.4, U5.18
D+/RB1: J4.15, J5.D+, U2.8
D+/RB2: J2.15, J6.D+, U1.8
D+/RB3: J8.15, J9.D+, U3.8
D+/RB4: J11.15, J12.D+, U4.8
D+/RB5: J14.15, J15.D+, U5.8
D-/RB1: J4.16, J5.D-, U2.9
D-/RB2: J2.16, J6.D-, U1.9
D-/RB3: J8.16, J9.D-, U3.9
D-/RB4: J11.16, J12.D-, U4.9
D-/RB5: J14.16, J15.D-, U5.9
GND1: C6.2, C7.2, C11.2, C12.2, C16.2, C17.2, C18.1, C19.1, C20.1, C21.1, C22.2, IC2.1, ICSP1.3, J3.2, J4.19, J5.GND, J5.MTN1, J5.MTN2, J5.MTN3, J5.MTN4, LED4.C, PROGRAM1.1, PROGRAM1.2, R2.2, RESET1.1, RESET1.2, U2.6, U2.16, U2.29, U2.39
GND2: C1.2, C2.2, C3.2, C4.2, C5.2, C8.2, C9.1, C10.1, C13.1, C14.1, C15.2, IC1.1, ICSP2.3, J1.2, J2.19, J6.GND, J6.MTN1, J6.MTN2, J6.MTN3, J6.MTN4, LED2.C, PROGRAM2.1, PROGRAM2.2, R1.2, RESET2.1, RESET2.2, U1.6, U1.16, U1.29, U1.39
GND3: C23.2, C24.2, C25.2, C26.2, C27.2, C28.2, C29.1, C30.1, C31.1, C32.1, C33.2, IC3.1, ICSP3.3, J7.2, J8.19, J9.GND, J9.MTN1, J9.MTN2, J9.MTN3, J9.MTN4, LED6.C, PROGRAM3.1, PROGRAM3.2, R11.2, RESET3.1, RESET3.2, U3.6, U3.16, U3.29, U3.39
GND4: C34.2, C35.2, C36.2, C37.2, C38.2, C39.2, C40.1, C41.1, C42.1, C43.1, C44.2, IC4.1, ICSP4.3, J10.2, J11.19, J12.GND, J12.MTN1, J12.MTN2, J12.MTN3, J12.MTN4, LED8.C, PROGRAM4.1, PROGRAM4.2, R16.2, RESET4.1, RESET4.2, U4.6, U4.16, U4.29, U4.39
GND5: C45.2, C46.2, C47.2, C48.2, C49.2, C50.2, C51.1, C52.1, C53.1, C54.1, C55.2, IC5.1, ICSP5.3, J13.2, J14.19, J15.GND, J15.MTN1, J15.MTN2, J15.MTN3, J15.MTN4, LED10.C, PROGRAM5.1, PROGRAM5.2, R21.2, RESET5.1, RESET5.2, U5.6, U5.16, U5.29, U5.39
unnamed: LED3.C, R2.1
unnamed: LED4.A, R5.1
unnamed: LED1.C, R1.1
unnamed: LED2.A, R9.1
unnamed: LED5.C, R11.1
unnamed: LED6.A, R14.1
unnamed: LED7.C, R16.1
unnamed: LED8.A, R19.1
unnamed: LED9.C, R21.1
unnamed: LED10.A, R24.1
RA1: C10.2, J1.19, Q1.2, U1.31
RA2: C9.2, J1.18, Q1.1, U1.30
RA3: J2.3, U1.35
RA4: J1.20, PROGRAM2.3, R10.2, U1.32
RA5: C19.2, J3.19, Q3.2, U2.31
RA6: C18.2, J3.18, Q3.1, U2.30
RA7: J1.5, LED1.A, U1.12
RA8: J1.6, U1.13
RA9: J1.9, U1.19
RA10: J1.10, U1.20
RA11: J4.3, U2.35
RA12: J3.20, PROGRAM1.3, R6.2, U2.32
RA13: J3.5, LED3.A, U2.12
RA14: J3.6, U2.13
RA15: J3.9, U2.19
RA16: J3.10, U2.20
RA17: C21.2, J4.2, Q4.1, U2.34
RA18: C14.2, J2.2, Q2.1, U1.34
RA19: C30.2, J7.19, Q5.2, U3.31
RA20: C29.2, J7.18, Q5.1, U3.30
RA21: J8.3, U3.35
RA22: J7.20, PROGRAM3.3, R15.2, U3.32
RA23: J7.5, LED5.A, U3.12
RA24: J7.6, U3.13
RA25: J7.9, U3.19
RA26: J7.10, U3.20
RA27: C32.2, J8.2, Q6.1, U3.34
RA28: C41.2, J10.19, Q7.2, U4.31
RA29: C40.2, J10.18, Q7.1, U4.30
RA30: J11.3, U4.35
RA31: J10.20, PROGRAM4.3, R20.2, U4.32
RA32: J10.5, LED7.A, U4.12
RA33: J10.6, U4.13
RA34: J10.9, U4.19
RA35: J10.10, U4.20
RA36: C43.2, J11.2, Q8.1, U4.34
RA37: C52.2, J13.19, Q9.2, U5.31
RA38: C51.2, J13.18, Q9.1, U5.30
RA39: J14.3, U5.35
RA40: J13.20, PROGRAM5.3, R25.2, U5.32
RA41: J13.5, LED9.A, U5.12
RA42: J13.6, U5.13
RA43: J13.9, U5.19
RA44: J13.10, U5.20
RA45: C54.2, J14.2, Q10.1, U5.34
RB1: J2.9, U1.44
RB2: J2.10, U1.1
RB3: J1.4, U1.11
RB4: J1.7, U1.14
RB5: J4.9, U2.44
RB6: J4.10, U2.1
RB7: J1.8, U1.15
RB8: ICSP2.5, J1.12, U1.22
RB9: ICSP2.4, J1.11, U1.21
RB10: J3.4, U2.11
RB11: J3.7, U2.14
RB12: J3.8, U2.15
RB13: J2.8, U1.43
RB14: J1.14, U1.24
RB15: J1.13, U1.23
RB16: ICSP1.5, J3.12, U2.22
RB17: ICSP1.4, J3.11, U2.21
RB18: J4.8, U2.43
RB19: J3.14, U2.24
RB20: J3.13, U2.23
RB21: C20.2, J4.1, Q4.2, U2.33
RB22: C13.2, J2.1, Q2.2, U1.33
RB23: J8.9, U3.44
RB24: J8.10, U3.1
RB25: J7.4, U3.11
RB26: J7.7, U3.14
RB27: J7.8, U3.15
RB28: ICSP3.5, J7.12, U3.22
RB29: ICSP3.4, J7.11, U3.21
RB30: J8.8, U3.43
RB31: J7.14, U3.24
RB32: J7.13, U3.23
RB33: C31.2, J8.1, Q6.2, U3.33
RB34: J11.9, U4.44
RB35: J11.10, U4.1
RB36: J10.4, U4.11
RB37: J10.7, U4.14
RB38: J10.8, U4.15
RB39: ICSP4.5, J10.12, U4.22
RB40: ICSP4.4, J10.11, U4.21
RB41: J11.8, U4.43
RB42: J10.14, U4.24
RB43: J10.13, U4.23
RB44: C42.2, J11.1, Q8.2, U4.33
RB45: J14.9, U5.44
RB46: J14.10, U5.1
RB47: J13.4, U5.11
RB48: J13.7, U5.14
RB49: J13.8, U5.15
RB50: ICSP5.5, J13.12, U5.22
RB51: ICSP5.4, J13.11, U5.21
RB52: J14.8, U5.43
RB53: J13.14, U5.24
RB54: J13.13, U5.23
RB55: C53.2, J14.1, Q10.2, U5.33
RC1: J2.6, U1.38
RC2: J2.5, U1.37
RC3: J2.4, U1.36
RC4: J1.17, U1.27
RC5: J1.16, U1.26
RC6: J1.15, U1.25
RC7: J2.11, U1.2
RC8: J2.12, U1.3
RC9: J2.13, U1.4
RC10: J4.6, U2.38
RC11: J4.5, U2.37
RC12: J4.4, U2.36
RC13: J3.17, U2.27
RC14: J3.16, U2.26
RC15: J3.15, U2.25
RC16: J4.11, U2.2
RC17: J4.12, U2.3
RC18: J4.13, U2.4
RC19: J4.14, U2.5
RC20: J2.14, U1.5
RC21: J8.6, U3.38
RC22: J8.5, U3.37
RC23: J8.4, U3.36
RC24: J7.17, U3.27
RC25: J7.16, U3.26
RC26: J7.15, U3.25
RC27: J8.11, U3.2
RC28: J8.12, U3.3
RC29: J8.13, U3.4
RC30: J8.14, U3.5
RC31: J11.6, U4.38
RC32: J11.5, U4.37
RC33: J11.4, U4.36
RC34: J10.17, U4.27
RC35: J10.16, U4.26
RC36: J10.15, U4.25
RC37: J11.11, U4.2
RC38: J11.12, U4.3
RC39: J11.13, U4.4
RC40: J11.14, U4.5
RC41: J14.6, U5.38
RC42: J14.5, U5.37
RC43: J14.4, U5.36
RC44: J13.17, U5.27
RC45: J13.16, U5.26
RC46: J13.15, U5.25
RC47: J14.11, U5.2
RC48: J14.12, U5.3
RC49: J14.13, U5.4
RC50: J14.14, U5.5
USBID/RB1: J4.7, J5.ID, R3.1, U2.41
USBID/RB2: J2.7, J6.ID, R7.1, U1.41
USBID/RB3: J8.7, J9.ID, R12.1, U3.41
USBID/RB4: J11.7, J12.ID, R17.1, U4.41
USBID/RB5: J14.7, J15.ID, R22.1, U5.41
VBUS1: D3.2, J5.VBUS
VBUS2: D1.2, J6.VBUS
VBUS3: D5.2, J9.VBUS
VBUS4: D7.2, J12.VBUS
VBUS5: D9.2, J15.VBUS
VCAP1: C6.1, C22.1, U2.7
VCAP2: C1.1, C15.1, U1.7
VCAP3: C23.1, C33.1, U3.7
VCAP4: C34.1, C44.1, U4.7
VCAP5: C45.1, C55.1, U5.7
VIN1: D4.2, J4.20
VIN2: D2.2, J2.20
VIN3: D6.2, J8.20
VIN4: D8.2, J11.20
VIN5: D10.2, J14.20

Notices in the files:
mini/v11/FubarinoMini_v11.sch:
licenced under Creative Commons v3.0 Attribution licence
parts and their libraries:
SparkFun-PowerIC: Licensing: CC v3.0 Share-Alike You are welcome to use this library for commercial purposes.
